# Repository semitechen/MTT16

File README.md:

**⚠️WARNING⚠️**  
This is a "Work in progress" project.
Read all the documentation before proceeding with development.

# Hardware Tracker MIDI Sequencer

A hardware-style MIDI sequencer designed for DJs and home producers. This device combines tactile control with powerful features to streamline music creation and performance.

---

## Features

### 🎵 Tracks & MIDI Control
- **16 Tracks**: Each track consists of 4 bytes:  
  - **Byte 1**: Type and channel  
  - **Byte 2**: Data byte 1 (note) 
  - **Byte 3**: Data byte 2 (velocity)
  - **Byte 4**: Delay  
- **Editing**: Tracks can be edited and muted via dedicated keypads.

### 🔄 Magnetic Encoder & Sync Control
- **Magnetic Encoder**:  
  - Control track position.  
  - Sync with song tempo "vinyl style".  
  - **Shift Key** under the encoder for alternate functions.  

### 🎚️ Tempo Control
- **Tempo Fader**: Fine-tune playback tempo.  
- **Tempo Modes**:  
  - Select tempo control range (+8, +16, wide) via buttons and LED indicators.

### ⌨️ Keypads & Modes
#### 16-Key Cherry MX Keypad
- **Modes**:  
  - Edit mode (upcoming functionality).  
  - Mute mode: Mute individual tracks.

#### 8-Key Cherry MX Keypad 
| Key        | Shift Function   | 
|------------|------------------|
| Cue        | Play             |
| A          | Edit             |
| B          | Mute             |
| Scene      | New Scene        |
| Nudge      | Tempo            |
| Copy       | Paste            |
| Delete     | Undo             |
| OK         | Duplicate        |

### 📟 Display
- **8x32 7-Segment LED Display**:  
  - Each character is 0.28".  
  - Displays key information across 4 columns in Scene Mode:  
    - Original tempo  
    - Scene  
    - A track  
    - B track  

### 🎛️ Scene Mode
- Use **OK Key** to select a scene and assign it to **Track A** or **Track B** via the **A** and **B** keys.  
- Each scene comprises 16 editable tracks.  
- Select and edit tracks using the **16-Key Keypad** in Edit Mode.  

---

## 📸 Photos
_Add photos here._  

---

## License
This project is licensed under the [Creative Commons Attribution-NonCommercial-ShareAlike 4.0 International License](https://creativecommons.org/licenses/by-nc-sa/4.0/).  

- You are free to build and modify the hardware and software for **non-commercial purposes**.  
- Commercial use of this project is strictly prohibited.

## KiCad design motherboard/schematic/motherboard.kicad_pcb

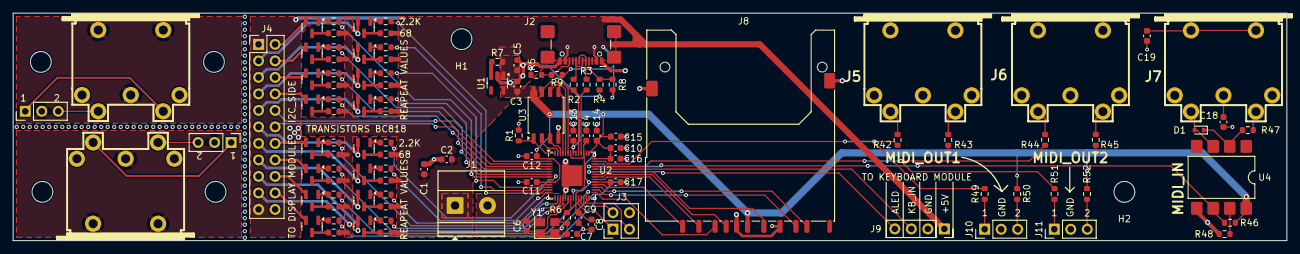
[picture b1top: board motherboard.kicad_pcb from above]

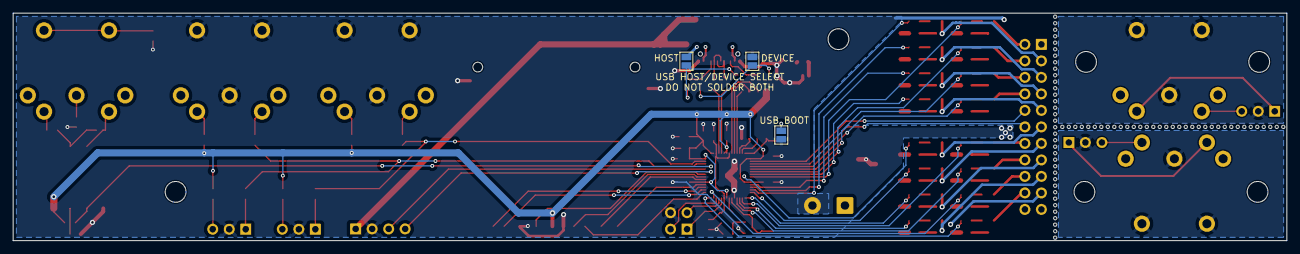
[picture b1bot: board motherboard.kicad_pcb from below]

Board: 2 copper layers, 196.0 x 35.0 mm, 117 parts (3 on the bottom side), 124 nets.

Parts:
C1: 100nF; C_0603_1608Metric
C2, C4, C5, C11: 1uF; C_0603_1608Metric
C3, C8, C9, C10, C12, C13, C14, C15, C16, C17: 0.1uF; C_0603_1608Metric
C6, C7: 15pF; C_0603_1608Metric
C18, C19: 0.1u; C_0603_1608Metric
D1: 1N4148WT; D_SOD-523
H1, H2: MountingHole; MountingHole_3.2mm_M3
H3, H4, H5, H6: Hole; MountingHole_3.2mm_M3
J1: Screw_Terminal_01x02; TerminalBlock_Phoenix_MKDS-1,5-2_1x02_P5.00mm_Horizontal
J2: USB_C_Receptacle_USB2.0_16P; USB_C_Receptacle_GCT_USB4110
J3: Conn_01x04; PinHeader_2x02_P2.54mm_Vertical
J4: Conn_02x11_Odd_Even; PinHeader_2x11_P2.54mm_Vertical
J5: MIDI_OUT1; MIDI_DIN5
J6: MIDI_OUT2; MIDI_DIN5
J7: MIDI_IN; MIDI_DIN5
J8: SD_Card_Receptacle; SD_Kyocera_145638009511859+
J9: Conn_01x04; PinSocket_1x04_P2.54mm_Vertical
J10, J11, J14, J15: Conn_01x03; PinHeader_1x03_P2.54mm_Vertical
J12, J13: MIDI_DIN5
JP1: USB_BOOT; SolderJumper-2_P1.3mm_Open_Pad1.0x1.5mm
JP2: DIVICE_MODE; SolderJumper-2_P1.3mm_Open_Pad1.0x1.5mm
JP3: HOST_MODE; SolderJumper-2_P1.3mm_Open_Pad1.0x1.5mm
Q1, Q2, Q3, Q4, Q5, Q6, Q7, Q8, Q9, Q10, Q11, Q12, Q13, Q14, Q15, Q16: BC818; SOT-23
R1, R6: 1K; R_0603_1608Metric
R2, R3: 27; R_0603_1608Metric
R4, R5: 5.1K; R_0603_1608Metric
R7: 10K; R_0603_1608Metric
R8, R9: 22K; R_0603_1608Metric
R10, R11, R12, R13, R18, R19, R20, R21, R26, R27, R28, R29, R34, R35, R36, R37: 68; R_0603_1608Metric
R14, R15, R16, R17, R22, R23, R24, R25, R30, R31, R32, R33, R38, R39, R40, R41, R46: 2.2K; R_0603_1608Metric
R42, R44, R49, R51: 10; R_0603_1608Metric
R43, R45, R50, R52: 33; R_0603_1608Metric
R47: 220; R_0603_1608Metric
R48: 4.7K; R_0603_1608Metric
U1: AP2112K-3.3; SOT-23-5
U2: RP2040; QFN-56-1EP_7x7mm_P0.4mm_EP3.2x3.2mm
U3: W25Q128JVS; SOIC-8_5.3x5.3mm_P1.27mm
U4: 6N138; SMDIP-8_W9.53mm
Y1: ABM8-272-T3; Crystal_SMD_Abracon_ABM8G-4Pin_3.2x2.5mm

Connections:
+1V1: C4.2, C8.1, C9.1, U2.23 (DVDD), U2.45 (VREG_VOUT), U2.50 (DVDD)
+3V3: C3.1, C10.1, C11.1, C12.1, C13.1, C14.1, C15.1, C16.1, C17.1, J8.4 (VDD), R43.1, R45.1, R46.1, R50.2, R52.2, U1.5 (VOUT), U2.1 (IOVDD), U2.10 (IOVDD), U2.22 (IOVDD), U2.33 (IOVDD), U2.42 (IOVDD), U2.43 (ADC_AVDD), U2.44 (VREG_IN), U2.48 (USB_VDD), U2.49 (IOVDD), U3.8 (VCC), U4.8 (VCC)
+5V: C1.2, C2.2, C5.1, J1.1, J2.A4 (VBUS), J2.A9 (VBUS), J2.B4 (VBUS), J2.B9 (VBUS), J4.19, J9.1, JP3.2 (B), R7.1, R10.1, R11.1, R12.1, R13.1, R18.1, R19.1, R20.1, R21.1, R26.1, R27.1, R28.1, R29.1, R34.1, R35.1, R36.1, R37.1, U1.1 (VIN)
/ALED: J9.4, U2.37 (GPIO25)
/DISPLAY_CONTROL/A1: R14.1, U2.8 (GPIO6)
/DISPLAY_CONTROL/A2: R15.1, U2.6 (GPIO4)
/DISPLAY_CONTROL/A3: R16.1, U2.5 (GPIO3)
/DISPLAY_CONTROL/A4: R17.1, U2.4 (GPIO2)
/DISPLAY_CONTROL/A5: R22.1, U2.16 (GPIO13)
/DISPLAY_CONTROL/A6: R23.1, U2.18 (GPIO15)
/DISPLAY_CONTROL/A7: R24.1, U2.27 (GPIO16)
/DISPLAY_CONTROL/A8: R25.1, U2.28 (GPIO17)
/DISPLAY_CONTROL/A9: R30.1, U2.13 (GPIO10)
/DISPLAY_CONTROL/A10: R31.1, U2.12 (GPIO9)
/DISPLAY_CONTROL/A11: R32.1, U2.11 (GPIO8)
/DISPLAY_CONTROL/A12: R33.1, U2.7 (GPIO5)
/DISPLAY_CONTROL/A13: R38.1, U2.9 (GPIO7)
/DISPLAY_CONTROL/A14: R39.1, U2.14 (GPIO11)
/DISPLAY_CONTROL/A15: R40.1, U2.15 (GPIO12)
/DISPLAY_CONTROL/A16: R41.1, U2.17 (GPIO14)
/DISPLAY_CONTROL/A_1: J4.2, Q1.2 (E)
/DISPLAY_CONTROL/A_2: J4.4, Q2.2 (E)
/DISPLAY_CONTROL/A_3: J4.6, Q3.2 (E)
/DISPLAY_CONTROL/A_4: J4.8, Q4.2 (E)
/DISPLAY_CONTROL/A_5: J4.14, Q5.2 (E)
/DISPLAY_CONTROL/A_6: J4.16, Q6.2 (E)
/DISPLAY_CONTROL/A_7: J4.18, Q7.2 (E)
/DISPLAY_CONTROL/A_8: J4.20, Q8.2 (E)
/DISPLAY_CONTROL/A_9: J4.3, Q9.2 (E)
/DISPLAY_CONTROL/A_10: J4.5, Q10.2 (E)
/DISPLAY_CONTROL/A_11: J4.7, Q11.2 (E)
/DISPLAY_CONTROL/A_12: J4.9, Q12.2 (E)
/DISPLAY_CONTROL/A_13: J4.11, Q13.2 (E)
/DISPLAY_CONTROL/A_14: J4.13, Q14.2 (E)
/DISPLAY_CONTROL/A_15: J4.15, Q15.2 (E)
/DISPLAY_CONTROL/A_16: J4.17, Q16.2 (E)
/DISPLAY_CONTROL/SCL: J4.12, U2.3 (GPIO1)
/DISPLAY_CONTROL/SDA: J4.10, U2.2 (GPIO0)
/GND1: J12.2, J12.6, J14.2
/GND2: J13.2, J13.6, J15.2
/KB_IN: J9.3, U2.38 (GPIO26_ADC0)
/MCU/CC1: J2.A5 (CC1), R4.1, R8.1
/MCU/CC2: J2.B5 (CC2), R5.1, R9.1
/MCU/GPIO18: J8.2 (CMD), U2.29 (GPIO18)
/MCU/GPIO19: J8.7 (DAT0), U2.30 (GPIO19)
/MCU/GPIO20: J8.8 (DAT1), U2.31 (GPIO20)
/MCU/GPIO21: J8.9 (DAT2), U2.32 (GPIO21)
/MCU/GPIO22: J8.1 (CD/DAT3), U2.34 (GPIO22)
/MCU/GPIO23: J8.10 (CARD_DETECT), U2.35 (GPIO23)
/MCU/GPIO24: J8.5 (CLK), U2.36 (GPIO24)
/MCU/GPIO27: R46.2, U2.39 (GPIO27_ADC1), U4.6 (VO2)
/MCU/QSPI_CS: R1.1, U2.56 (QSPI_SS), U3.1 (~CS)
/MCU/QSPI_SCK: U2.52 (QSPI_SCLK), U3.6 (CLK)
/MCU/QSPI_SD0: U2.53 (QSPI_SD0), U3.5 (DI/IO_{0})
/MCU/QSPI_SD1: U2.55 (QSPI_SD1), U3.2 (DO/IO_{1})
/MCU/QSPI_SD2: U2.54 (QSPI_SD2), U3.3 (~WP/IO_{2})
/MCU/QSPI_SD3: U2.51 (QSPI_SD3), U3.7 (~HOLD/~RESET/IO_{3})
/MCU/RUN: J3.3, U2.26 (RUN)
/MCU/SWCLK: J3.1, U2.24 (SWCLK)
/MCU/SWDIO: J3.2, U2.25 (SWD)
/MCU/USB_BOOT: JP1.1 (A), R1.2
/MCU/USB_N: J2.A7 (D-), J2.B7 (D-), R3.2
/MCU/USB_P: J2.A6 (D+), J2.B6 (D+), R2.2
/MCU/XIN: C6.1, U2.20 (XIN), Y1.1
/MCU/XOUT: R6.1, U2.21 (XOUT)
/MIDI_OUT1: R42.2, R49.2, U2.41 (GPIO29_ADC3)
/MIDI_OUT2: R44.2, R51.2, U2.40 (GPIO28_ADC2)
GND: C1.1, C2.1, C3.2, C4.1, C5.2, C6.2, C7.2, C8.2, C9.2, C10.2, C11.2, C12.2, C13.2, C14.2, C15.2, C16.2, C17.2, C18.1, C19.2, J1.2, J2.A1 (GND), J2.A12 (GND), J2.B1 (GND), J2.B12 (GND), J3.4, J4.1, J4.21, J5.2, J5.6, J6.2, J6.6, J8.3 (VSS), J8.6 (VSS), J8.12 (SHELL1), J8.13 (SHELL2), J9.2, J10.2, J11.2, JP1.2 (B), JP2.2 (B), R48.1, U1.2 (GND), U2.19 (TESTEN), U2.57 (GND), U3.4 (GND), U4.5 (GND), Y1.2, Y1.4
unnamed: C7.1, R6.2, Y1.3
unnamed: C18.2, J7.2
unnamed: C19.1, J7.6
unnamed: D1.2 (A), J7.4, U4.3 (C2)
unnamed: D1.1 (K), R47.2, U4.2 (C1)
unnamed: J5.4, R42.1
unnamed: J5.5, R43.2
unnamed: J6.4, R44.1
unnamed: J6.5, R45.2
unnamed: J7.5, R47.1
unnamed: J10.1, R49.1
unnamed: J10.3, R50.1
unnamed: J11.1, R51.1
unnamed: J11.3, R52.1
unnamed: J12.5, J14.1
unnamed: J12.4, J14.3
unnamed: J13.5, J15.1
unnamed: J13.4, J15.3
unnamed: JP2.1 (A), R4.2, R5.2
unnamed: JP3.1 (A), R8.2, R9.2
unnamed: Q1.1 (B), R14.2
unnamed: Q1.3 (C), R10.2
unnamed: Q2.1 (B), R15.2
unnamed: Q2.3 (C), R11.2
unnamed: Q3.1 (B), R16.2
unnamed: Q3.3 (C), R12.2
unnamed: Q4.1 (B), R17.2
unnamed: Q4.3 (C), R13.2
unnamed: Q5.1 (B), R22.2
unnamed: Q5.3 (C), R18.2
unnamed: Q6.1 (B), R23.2
unnamed: Q6.3 (C), R19.2
unnamed: Q7.1 (B), R24.2
unnamed: Q7.3 (C), R20.2
unnamed: Q8.1 (B), R25.2
unnamed: Q8.3 (C), R21.2
unnamed: Q9.1 (B), R30.2
unnamed: Q9.3 (C), R26.2
unnamed: Q10.1 (B), R31.2
unnamed: Q10.3 (C), R27.2
unnamed: Q11.1 (B), R32.2
unnamed: Q11.3 (C), R28.2
unnamed: Q12.1 (B), R33.2
unnamed: Q12.3 (C), R29.2
unnamed: Q13.1 (B), R38.2
unnamed: Q13.3 (C), R34.2
unnamed: Q14.1 (B), R39.2
unnamed: Q14.3 (C), R35.2
unnamed: Q15.1 (B), R40.2
unnamed: Q15.3 (C), R36.2
unnamed: Q16.1 (B), R41.2
unnamed: Q16.3 (C), R37.2
unnamed: R7.2, U1.3 (EN)
unnamed: R3.1, U2.46 (USB_DM)
unnamed: R2.1, U2.47 (USB_DP)
unnamed: R48.2, U4.7 (VO1)

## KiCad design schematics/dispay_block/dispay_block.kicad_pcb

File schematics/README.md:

# Hardware Tracker MIDI Sequencer

A hardware-style MIDI sequencer designed for DJs and home producers. This device combines tactile control with powerful features to streamline music creation and performance.

---

## Features

### 🎵 Tracks & MIDI Control
- **16 Tracks**: Each track consists of 4 bytes:  
  - **Byte 1**: Type and channel  
  - **Byte 2**: Data byte 1 (note) 
  - **Byte 3**: Data byte 2 (velocity)
  - **Byte 4**: Delay  
- **Editing**: Tracks can be edited and muted via dedicated keypads.

### 🔄 Magnetic Encoder & Sync Control
- **Magnetic Encoder**:  
  - Control track position.  
  - Sync with song tempo "vinyl style".  
  - **Shift Key** under the encoder for alternate functions.  

### 🎚️ Tempo Control
- **Tempo Fader**: Fine-tune playback tempo.  
- **Tempo Modes**:  
  - Select tempo control range (+8, +16, wide) via buttons and LED indicators.

### ⌨️ Keypads & Modes
#### 16-Key Cherry MX Keypad
- **Modes**:  
  - Edit mode (upcoming functionality).  
  - Mute mode: Mute individual tracks.

#### 8-Key Cherry MX Keypad 
| Key        | Shift Function   | 
|------------|------------------|
| Cue        | Play             |
| A          | Edit             |
| B          | Mute             |
| Scene      | New Scene        |
| Nudge      | Tempo            |
| Copy       | Paste            |
| Delete     | Undo             |
| OK         | Duplicate        |

### 📟 Display
- **8x32 7-Segment LED Display**:  
  - Each character is 0.28".  
  - Displays key information across 4 columns in Scene Mode:  
    - Original tempo  
    - Scene  
    - A track  
    - B track  

### 🎛️ Scene Mode
- Use **OK Key** to select a scene and assign it to **Track A** or **Track B** via the **A** and **B** keys.  
- Each scene comprises 16 editable tracks.  
- Select and edit tracks using the **16-Key Keypad** in Edit Mode.  

---

## 📸 Photos
_Add photos here._  

---

## License
This project is licensed under the [Creative Commons Attribution-NonCommercial-ShareAlike 4.0 International License](https://creativecommons.org/licenses/by-nc-sa/4.0/).  

- You are free to build and modify the hardware and software for **non-commercial purposes**.  
- Commercial use of this project is strictly prohibited.

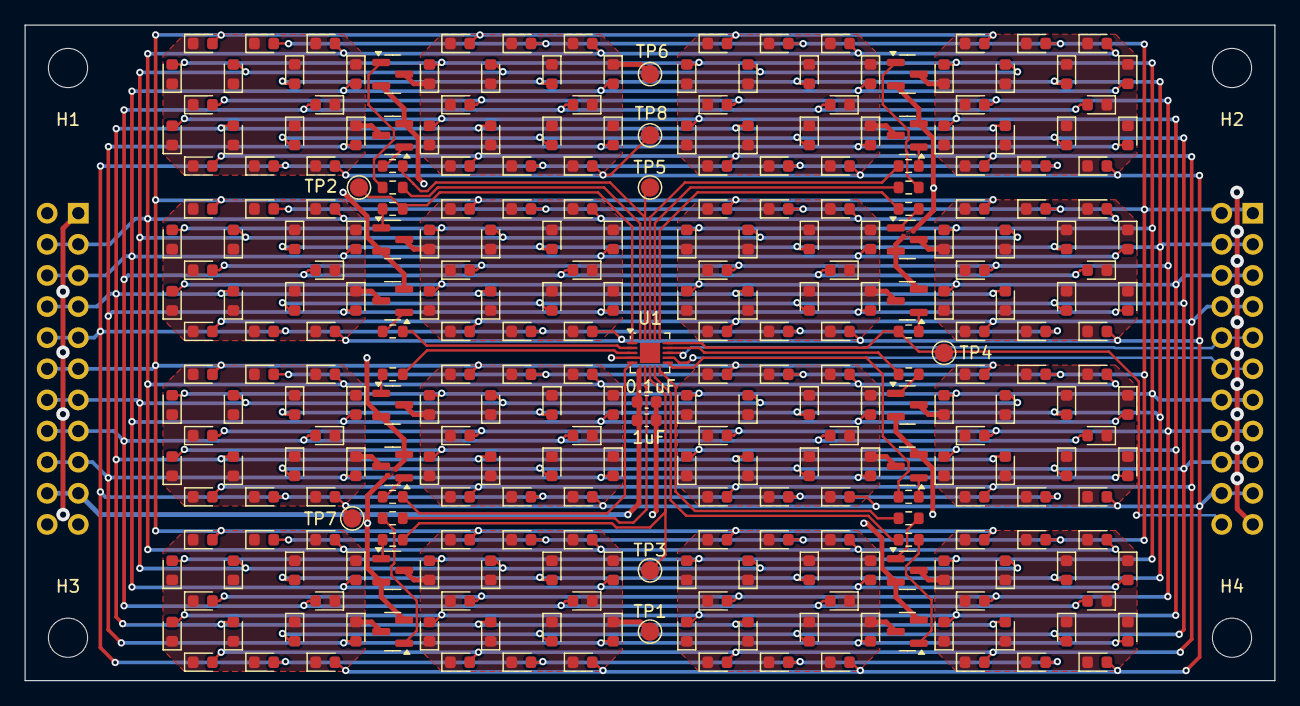
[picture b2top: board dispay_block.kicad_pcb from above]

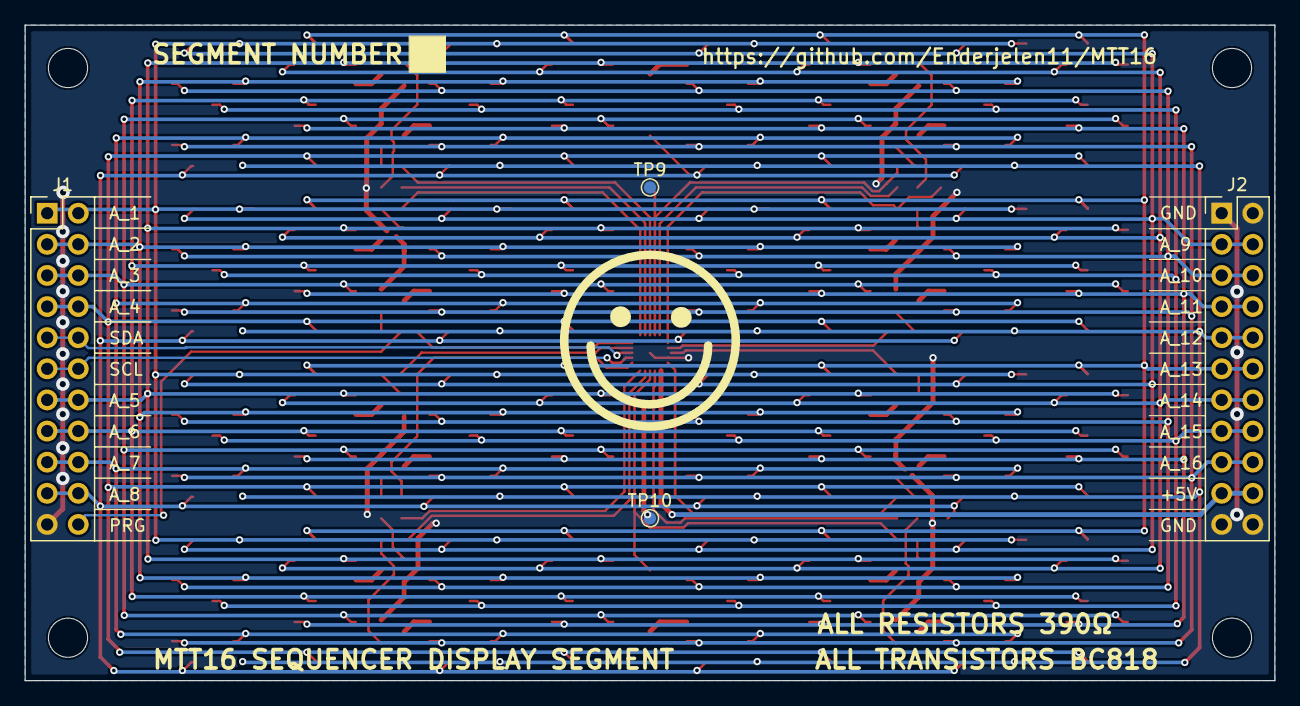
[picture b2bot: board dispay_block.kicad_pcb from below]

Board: 2 copper layers, 102.0 x 53.5 mm, 307 parts (4 on the bottom side), 68 nets.

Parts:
C1: 0.1uF; C_0603_1608Metric
C2: 1uF; C_0603_1608Metric
D1, D2, D3, D4, D5, D6, D7, D8, D9, D10, D11, D12, D13, D14, D15, D16, D17, D18, D19, D20, D21, D22, D23, D24, D25, D26, D27, D28, D29, D30, D31, D32, D33, D34, D35, D36, D37, D38, D39, D40, D41, D42, D43, D44, D45, D46, D47, D48, D49, D50, D51, D52, D53, D54, D55, D56, D57, D58, D59, D60, D61, D62, D63, D64, D65, D66, D67, D68, D69, D70, D71, D72, D73, D74, D75, D76, D77, D78, D79, D80, D81, D82, D83, D84, D85, D86, D87, D88, D89, D90, D91, D92, D93, D94, D95, D96, D97, D98, D99, D100, D101, D102, D103, D104, D105, D106, D107, D108, D109, D110, D111, D112, D113, D114, D115, D116, D117, D118, D119, D120, D121, D122, D123, D124, D125, D126, D127, D128, D129, D130, D131, D132, D133, D134, D135, D136, D137, D138, D139, D140, D141, D142, D143, D144, D145, D146, D147, D148, D149, D150, D151, D152, D153, D154, D155, D156, D157, D158, D159, D160, D161, D162, D163, D164, D165, D166, D167, D168, D169, D170, D171, D172, D173, D174, D175, D176, D177, D178, D179, D180, D181, D182, D183, D184, D185, D186, D187, D188, D189, D190, D191, D192, D193, D194, D195, D196, D197, D198, D199, D200, D201, D202, D203, D204, D205, D206, D207, D208, D209, D210, D211, D212, D213, D214, D215, D216, D217, D218, D219, D220, D221, D222, D223, D224, D225, D226, D227, D228, D229, D230, D231, D232, D233, D234, D235, D236, D237, D238, D239, D240, D241, D242, D243, D244, D245, D246, D247, D248, D249, D250, D251, D252, D253, D254, D255, D256: LED; LED_0603_1608Metric
H1, H2, H3, H4: MountingHole; MountingHole_3.2mm_M3
J1, J2: Conn_02x11_Odd_Even; PinHeader_2x11_P2.54mm_Vertical
Q1, Q2, Q3, Q4, Q5, Q6, Q7, Q8, Q9, Q10, Q11, Q12, Q13, Q14, Q15, Q16: BC818; SOT-23
R1, R2, R3, R4, R5, R6, R7, R8, R9, R10, R11, R12, R13, R14, R15, R16: 390; R_0603_1608Metric
TP1: CC13; TestPoint_Pad_D1.5mm
TP2: RESET; TestPoint_Pad_D1.5mm
TP3: PC1; TestPoint_Pad_D1.5mm
TP4: PD1(SWIO); TestPoint_Pad_D1.5mm
TP5: PD5(TX); TestPoint_Pad_D1.5mm
TP6: CC2; TestPoint_Pad_D1.5mm
TP7, TP8: B8; TestPoint_Pad_D1.5mm
TP9, TP10: GND; TestPoint_Pad_D1.0mm
U1: CH32V003FxUx; QFN-20-1EP_3x3mm_P0.4mm_EP1.65x1.65mm

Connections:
+5V: C1.2, C2.2, J2.19, J2.20, U1.6 (VDD)
/CC1: D1.1 (K), D2.1 (K), D3.1 (K), D4.1 (K), D5.1 (K), D6.1 (K), D7.1 (K), D8.1 (K), D9.1 (K), D10.1 (K), D11.1 (K), D12.1 (K), D13.1 (K), D14.1 (K), D15.1 (K), D16.1 (K), Q4.3 (C)
/CC2: D17.1 (K), D18.1 (K), D19.1 (K), D20.1 (K), D21.1 (K), D22.1 (K), D23.1 (K), D24.1 (K), D25.1 (K), D26.1 (K), D27.1 (K), D28.1 (K), D29.1 (K), D30.1 (K), D31.1 (K), D32.1 (K), Q5.3 (C), TP6.1
/CC3: D33.1 (K), D34.1 (K), D35.1 (K), D36.1 (K), D37.1 (K), D38.1 (K), D39.1 (K), D40.1 (K), D41.1 (K), D42.1 (K), D43.1 (K), D44.1 (K), D45.1 (K), D46.1 (K), D47.1 (K), D48.1 (K), Q8.3 (C)
/CC4: D49.1 (K), D50.1 (K), D51.1 (K), D52.1 (K), D53.1 (K), D54.1 (K), D55.1 (K), D56.1 (K), D57.1 (K), D58.1 (K), D59.1 (K), D60.1 (K), D61.1 (K), D62.1 (K), D63.1 (K), D64.1 (K), Q7.3 (C)
/CC5: D65.1 (K), D66.1 (K), D67.1 (K), D68.1 (K), D69.1 (K), D70.1 (K), D71.1 (K), D72.1 (K), D73.1 (K), D74.1 (K), D75.1 (K), D76.1 (K), D77.1 (K), D78.1 (K), D79.1 (K), D80.1 (K), Q14.3 (C)
/CC6: D81.1 (K), D82.1 (K), D83.1 (K), D84.1 (K), D85.1 (K), D86.1 (K), D87.1 (K), D88.1 (K), D89.1 (K), D90.1 (K), D91.1 (K), D92.1 (K), D93.1 (K), D94.1 (K), D95.1 (K), D96.1 (K), Q9.3 (C)
/CC7: D97.1 (K), D98.1 (K), D99.1 (K), D100.1 (K), D101.1 (K), D102.1 (K), D103.1 (K), D104.1 (K), D105.1 (K), D106.1 (K), D107.1 (K), D108.1 (K), D109.1 (K), D110.1 (K), D111.1 (K), D112.1 (K), Q10.3 (C)
/CC8: D113.1 (K), D114.1 (K), D115.1 (K), D116.1 (K), D117.1 (K), D118.1 (K), D119.1 (K), D120.1 (K), D121.1 (K), D122.1 (K), D123.1 (K), D124.1 (K), D125.1 (K), D126.1 (K), D127.1 (K), D128.1 (K), Q1.3 (C)
/CC9: D129.1 (K), D130.1 (K), D131.1 (K), D132.1 (K), D133.1 (K), D134.1 (K), D135.1 (K), D136.1 (K), D137.1 (K), D138.1 (K), D139.1 (K), D140.1 (K), D141.1 (K), D142.1 (K), D143.1 (K), D144.1 (K), Q6.3 (C)
/CC10: D145.1 (K), D146.1 (K), D147.1 (K), D148.1 (K), D149.1 (K), D150.1 (K), D151.1 (K), D152.1 (K), D153.1 (K), D154.1 (K), D155.1 (K), D156.1 (K), D157.1 (K), D158.1 (K), D159.1 (K), D160.1 (K), Q16.3 (C)
/CC11: D161.1 (K), D162.1 (K), D163.1 (K), D164.1 (K), D165.1 (K), D166.1 (K), D167.1 (K), D168.1 (K), D169.1 (K), D170.1 (K), D171.1 (K), D172.1 (K), D173.1 (K), D174.1 (K), D175.1 (K), D176.1 (K), Q11.3 (C)
/CC12: D177.1 (K), D178.1 (K), D179.1 (K), D180.1 (K), D181.1 (K), D182.1 (K), D183.1 (K), D184.1 (K), D185.1 (K), D186.1 (K), D187.1 (K), D188.1 (K), D189.1 (K), D190.1 (K), D191.1 (K), D192.1 (K), Q2.3 (C)
/CC13: D193.1 (K), D194.1 (K), D195.1 (K), D196.1 (K), D197.1 (K), D198.1 (K), D199.1 (K), D200.1 (K), D201.1 (K), D202.1 (K), D203.1 (K), D204.1 (K), D205.1 (K), D206.1 (K), D207.1 (K), D208.1 (K), Q12.3 (C), TP1.1
/CC14: D209.1 (K), D210.1 (K), D211.1 (K), D212.1 (K), D213.1 (K), D214.1 (K), D215.1 (K), D216.1 (K), D217.1 (K), D218.1 (K), D219.1 (K), D220.1 (K), D221.1 (K), D222.1 (K), D223.1 (K), D224.1 (K), Q13.3 (C)
/CC15: D225.1 (K), D226.1 (K), D227.1 (K), D228.1 (K), D229.1 (K), D230.1 (K), D231.1 (K), D232.1 (K), D233.1 (K), D234.1 (K), D235.1 (K), D236.1 (K), D237.1 (K), D238.1 (K), D239.1 (K), D240.1 (K), Q15.3 (C)
/CC16: D241.1 (K), D242.1 (K), D243.1 (K), D244.1 (K), D245.1 (K), D246.1 (K), D247.1 (K), D248.1 (K), D249.1 (K), D250.1 (K), D251.1 (K), D252.1 (K), D253.1 (K), D254.1 (K), D255.1 (K), D256.1 (K), Q3.3 (C)
/SCL: J1.11, J1.12, U1.12 (SCL_2)
/SDA: J1.9, J1.10, U1.13 (SDA_2)
/SWIO: J1.22, R13.1, TP4.1, U1.15 (PD1)
A_1: D2.2 (A), D18.2 (A), D34.2 (A), D50.2 (A), D66.2 (A), D82.2 (A), D98.2 (A), D114.2 (A), D130.2 (A), D146.2 (A), D162.2 (A), D178.2 (A), D194.2 (A), D210.2 (A), D226.2 (A), D242.2 (A), J1.1, J1.2
A_2: D6.2 (A), D22.2 (A), D38.2 (A), D54.2 (A), D70.2 (A), D86.2 (A), D102.2 (A), D118.2 (A), D134.2 (A), D150.2 (A), D166.2 (A), D182.2 (A), D198.2 (A), D214.2 (A), D230.2 (A), D246.2 (A), J1.3, J1.4
A_3: D10.2 (A), D26.2 (A), D42.2 (A), D58.2 (A), D74.2 (A), D90.2 (A), D106.2 (A), D122.2 (A), D138.2 (A), D154.2 (A), D170.2 (A), D186.2 (A), D202.2 (A), D218.2 (A), D234.2 (A), D250.2 (A), J1.5, J1.6
A_4: D14.2 (A), D30.2 (A), D46.2 (A), D62.2 (A), D78.2 (A), D94.2 (A), D110.2 (A), D126.2 (A), D142.2 (A), D158.2 (A), D174.2 (A), D190.2 (A), D206.2 (A), D222.2 (A), D238.2 (A), D254.2 (A), J1.7, J1.8
A_5: D4.2 (A), D20.2 (A), D36.2 (A), D52.2 (A), D68.2 (A), D84.2 (A), D100.2 (A), D116.2 (A), D132.2 (A), D148.2 (A), D164.2 (A), D180.2 (A), D196.2 (A), D212.2 (A), D228.2 (A), D244.2 (A), J1.13, J1.14
A_6: D8.2 (A), D24.2 (A), D40.2 (A), D56.2 (A), D72.2 (A), D88.2 (A), D104.2 (A), D120.2 (A), D136.2 (A), D152.2 (A), D168.2 (A), D184.2 (A), D200.2 (A), D216.2 (A), D232.2 (A), D248.2 (A), J1.15, J1.16
A_7: D12.2 (A), D28.2 (A), D44.2 (A), D60.2 (A), D76.2 (A), D92.2 (A), D108.2 (A), D124.2 (A), D140.2 (A), D156.2 (A), D172.2 (A), D188.2 (A), D204.2 (A), D220.2 (A), D236.2 (A), D252.2 (A), J1.17, J1.18
A_8: D16.2 (A), D32.2 (A), D48.2 (A), D64.2 (A), D80.2 (A), D96.2 (A), D112.2 (A), D128.2 (A), D144.2 (A), D160.2 (A), D176.2 (A), D192.2 (A), D208.2 (A), D224.2 (A), D240.2 (A), D256.2 (A), J1.19, J1.20, TP7.1, TP8.1
A_9: D3.2 (A), D19.2 (A), D35.2 (A), D51.2 (A), D67.2 (A), D83.2 (A), D99.2 (A), D115.2 (A), D131.2 (A), D147.2 (A), D163.2 (A), D179.2 (A), D195.2 (A), D211.2 (A), D227.2 (A), D243.2 (A), J2.3, J2.4
A_10: D7.2 (A), D23.2 (A), D39.2 (A), D55.2 (A), D71.2 (A), D87.2 (A), D103.2 (A), D119.2 (A), D135.2 (A), D151.2 (A), D167.2 (A), D183.2 (A), D199.2 (A), D215.2 (A), D231.2 (A), D247.2 (A), J2.5, J2.6
A_11: D11.2 (A), D27.2 (A), D43.2 (A), D59.2 (A), D75.2 (A), D91.2 (A), D107.2 (A), D123.2 (A), D139.2 (A), D155.2 (A), D171.2 (A), D187.2 (A), D203.2 (A), D219.2 (A), D235.2 (A), D251.2 (A), J2.7, J2.8
A_12: D15.2 (A), D31.2 (A), D47.2 (A), D63.2 (A), D79.2 (A), D95.2 (A), D111.2 (A), D127.2 (A), D143.2 (A), D159.2 (A), D175.2 (A), D191.2 (A), D207.2 (A), D223.2 (A), D239.2 (A), D255.2 (A), J2.9, J2.10
A_13: D1.2 (A), D17.2 (A), D33.2 (A), D49.2 (A), D65.2 (A), D81.2 (A), D97.2 (A), D113.2 (A), D129.2 (A), D145.2 (A), D161.2 (A), D177.2 (A), D193.2 (A), D209.2 (A), D225.2 (A), D241.2 (A), J2.11, J2.12
A_14: D5.2 (A), D21.2 (A), D37.2 (A), D53.2 (A), D69.2 (A), D85.2 (A), D101.2 (A), D117.2 (A), D133.2 (A), D149.2 (A), D165.2 (A), D181.2 (A), D197.2 (A), D213.2 (A), D229.2 (A), D245.2 (A), J2.13, J2.14
A_15: D9.2 (A), D25.2 (A), D41.2 (A), D57.2 (A), D73.2 (A), D89.2 (A), D105.2 (A), D121.2 (A), D137.2 (A), D153.2 (A), D169.2 (A), D185.2 (A), D201.2 (A), D217.2 (A), D233.2 (A), D249.2 (A), J2.15, J2.16
A_16: D13.2 (A), D29.2 (A), D45.2 (A), D61.2 (A), D77.2 (A), D93.2 (A), D109.2 (A), D125.2 (A), D141.2 (A), D157.2 (A), D173.2 (A), D189.2 (A), D205.2 (A), D221.2 (A), D237.2 (A), D253.2 (A), J2.17, J2.18
GND: C1.1, C2.1, J1.21, J2.1, J2.2, J2.21, J2.22, Q1.2 (E), Q2.2 (E), Q3.2 (E), Q4.2 (E), Q5.2 (E), Q6.2 (E), Q7.2 (E), Q8.2 (E), Q9.2 (E), Q10.2 (E), Q11.2 (E), Q12.2 (E), Q13.2 (E), Q14.2 (E), Q15.2 (E), Q16.2 (E), TP9.1, TP10.1, U1.4 (VSS), U1.21 (VSS)
unnamed: Q1.1 (B), R5.2
unnamed: Q2.1 (B), R1.2
unnamed: Q3.1 (B), R15.1
unnamed: Q4.1 (B), R3.1
unnamed: Q5.1 (B), R4.1
unnamed: Q6.1 (B), R6.2
unnamed: Q7.1 (B), R7.2
unnamed: Q8.1 (B), R9.1
unnamed: Q9.1 (B), R11.1
unnamed: Q10.1 (B), R13.2
unnamed: Q11.1 (B), R14.2
unnamed: Q12.1 (B), R12.1
unnamed: Q13.1 (B), R10.2
unnamed: Q14.1 (B), R8.2
unnamed: Q15.1 (B), R2.1
unnamed: Q16.1 (B), R16.2
unnamed: R8.1, U1.2 (PA1)
unnamed: R16.1, U1.3 (PA2)
unnamed: R10.1, U1.7 (PC0)
unnamed: R12.2, TP3.1, U1.8 (PC1)
unnamed: R2.2, U1.9 (PC2)
unnamed: R15.2, U1.10 (PC3)
unnamed: R14.1, U1.11 (PC4)
unnamed: R1.1, U1.14 (PC7)
unnamed: R6.1, U1.5 (PD0)
unnamed: R5.1, U1.16 (PD2)
unnamed: R7.1, U1.17 (PD3)
unnamed: R9.2, U1.18 (PD4)
unnamed: R3.2, TP5.1, U1.19 (PD5)
unnamed: R4.2, U1.20 (PD6)
unnamed: R11.2, TP2.1, U1.1 (PD7)

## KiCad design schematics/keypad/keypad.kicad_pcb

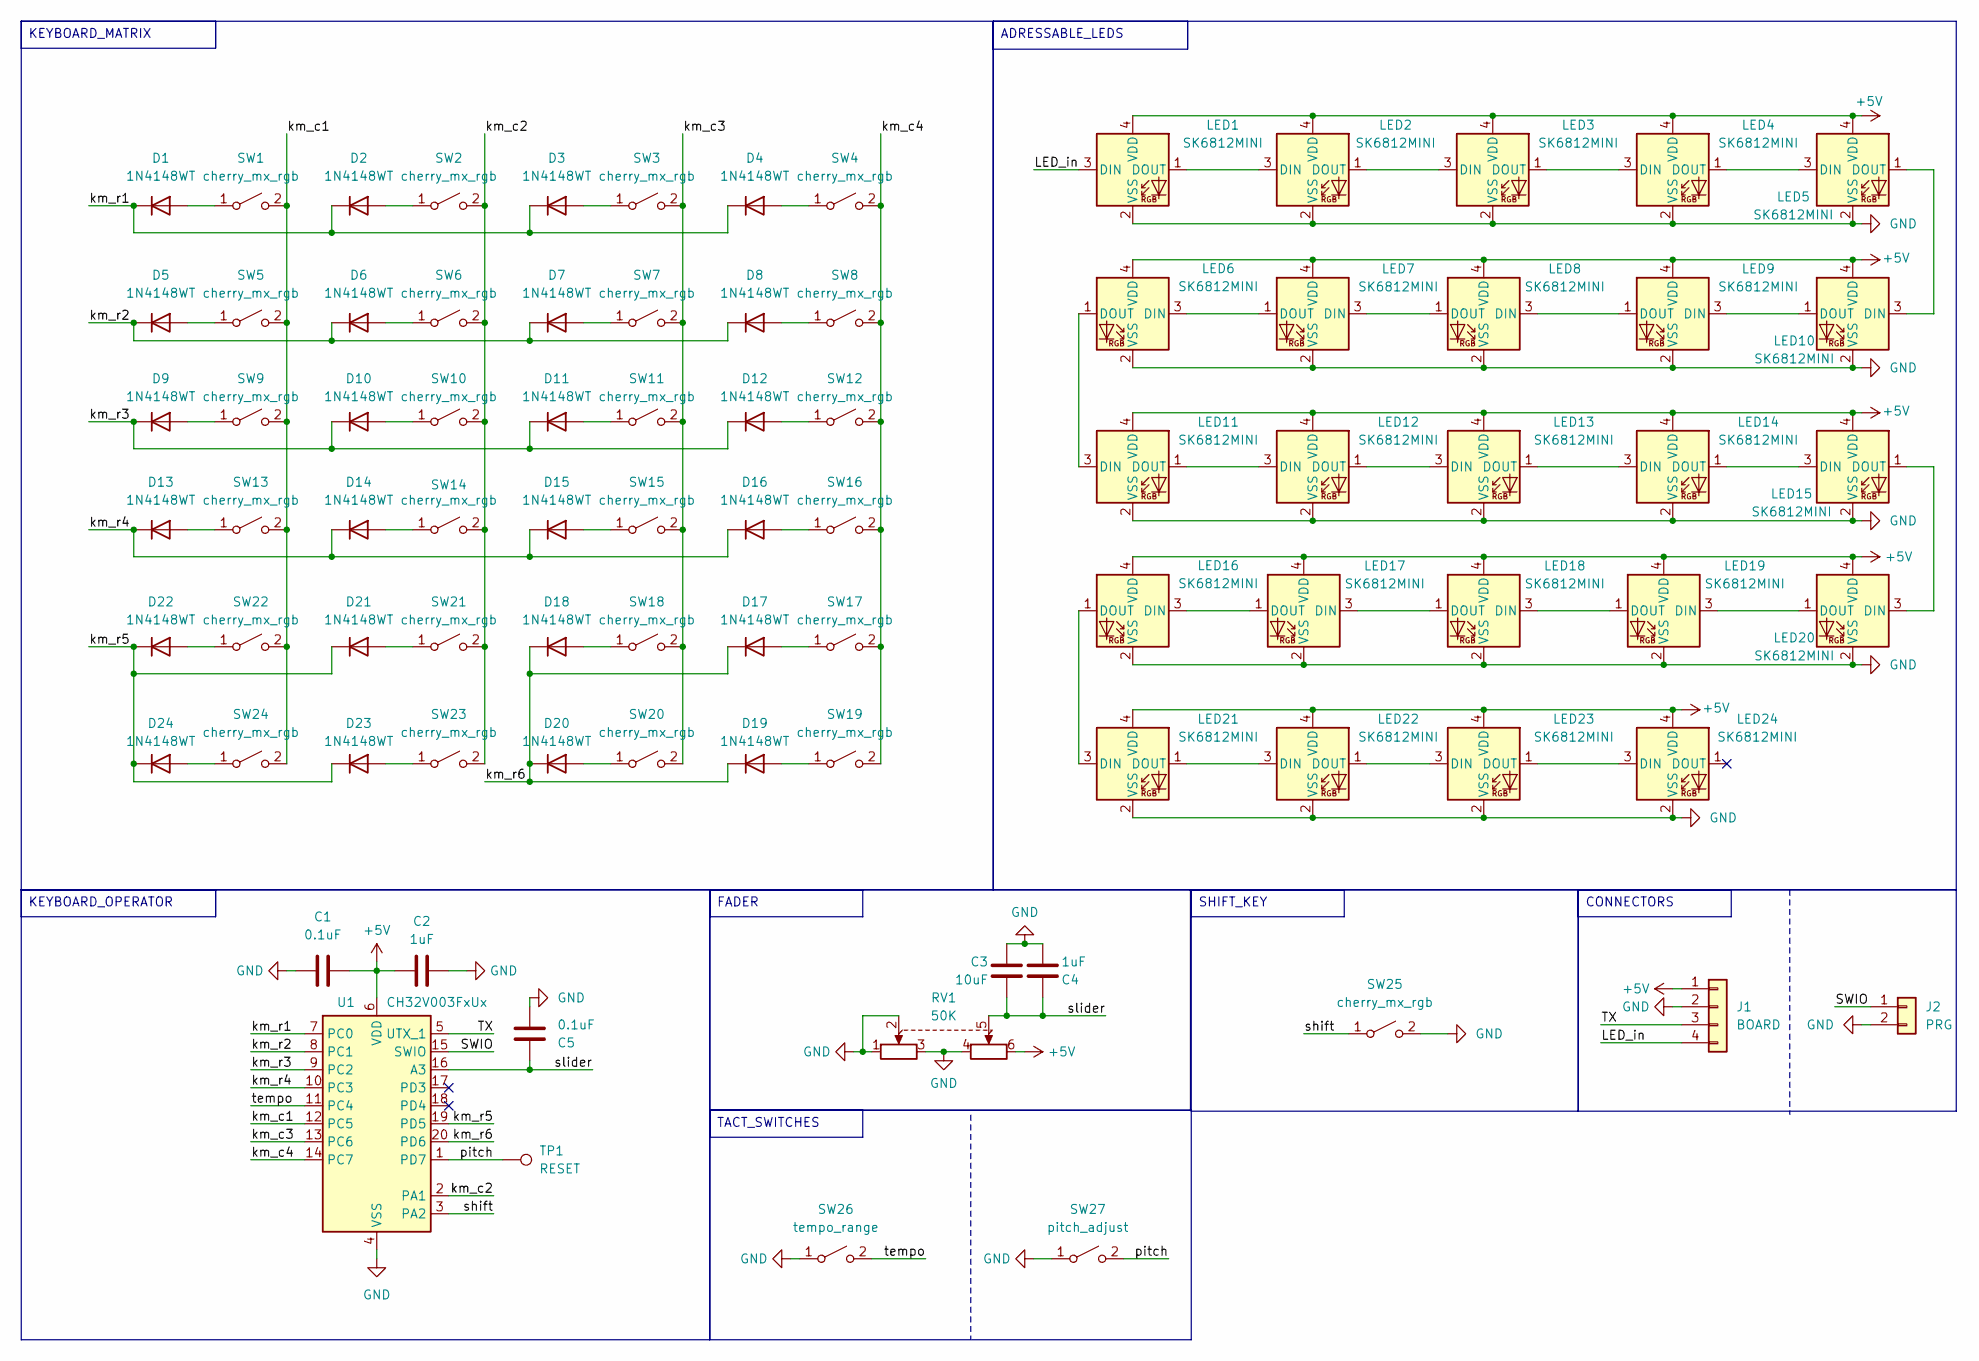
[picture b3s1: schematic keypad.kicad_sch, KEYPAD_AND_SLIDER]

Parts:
C1, C5: 0.1uF; C_0603_1608Metric
C2, C4: 1uF; C_0603_1608Metric
C3: 10uF; C_0603_1608Metric
D1, D2, D3, D4, D5, D6, D7, D8, D9, D10, D11, D12, D13, D14, D15, D16, D17, D18, D19, D20, D21, D22, D23, D24: 1N4148WT; D_SOD-523
J1: BOARD; PinHeader_1x04_P2.54mm_Horizontal; Part Number 1-0401FBV0T
J2: PRG; PinHeader_1x02_P2.54mm_Vertical; Part Number 1-0201FBV0T
LED1, LED2, LED3, LED4, LED5, LED6, LED7, LED8, LED9, LED10, LED11, LED12, LED13, LED14, LED15, LED16, LED17, LED18, LED19, LED20, LED21, LED22, LED23, LED24: SK6812MINI; SK6812-MINI-E
RV1: 50K; 75mm_slide_pot
SW1, SW2, SW3, SW4, SW5, SW6, SW7, SW8, SW9, SW10, SW11, SW12, SW13, SW14, SW15, SW16, SW17, SW18, SW19, SW20, SW21, SW22, SW23, SW24: cherry_mx_rgb; SW_Hotswap_Kailh_MX_1.00u
SW25: cherry_mx_rgb; SW_Hotswap_Kailh_MX_2.00u
SW26: tempo_range; tact_switch
SW27: pitch_adjust; tact_switch
TP1: RESET
U1: CH32V003FxUx; QFN-20-1EP_3x3mm_P0.4mm_EP1.65x1.65mm

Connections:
+5V: C1.2, C2.2, J1.1, LED1.4 (VDD), LED2.4 (VDD), LED3.4 (VDD), LED4.4 (VDD), LED5.4 (VDD), LED6.4 (VDD), LED7.4 (VDD), LED8.4 (VDD), LED9.4 (VDD), LED10.4 (VDD), LED11.4 (VDD), LED12.4 (VDD), LED13.4 (VDD), LED14.4 (VDD), LED15.4 (VDD), LED16.4 (VDD), LED17.4 (VDD), LED18.4 (VDD), LED19.4 (VDD), LED20.4 (VDD), LED21.4 (VDD), LED22.4 (VDD), LED23.4 (VDD), LED24.4 (VDD), RV1.6, U1.6 (VDD)
/LED_in: J1.4, LED1.3 (DIN)
/SWIO: J2.1, U1.15 (SWIO)
/TX: J1.3, U1.5 (UTX_1)
/km_c1: SW1.2 (B), SW5.2 (B), SW9.2 (B), SW13.2 (B), SW22.2 (B), SW24.2 (B), U1.12 (PC5)
/km_c2: SW2.2 (B), SW6.2 (B), SW10.2 (B), SW14.2 (B), SW21.2 (B), SW23.2 (B), U1.2 (PA1)
/km_c3: SW3.2 (B), SW7.2 (B), SW11.2 (B), SW15.2 (B), SW18.2 (B), SW20.2 (B), U1.13 (PC6)
/km_c4: SW4.2 (B), SW8.2 (B), SW12.2 (B), SW16.2 (B), SW17.2 (B), SW19.2 (B), U1.14 (PC7)
/km_r1: D1.1 (K), D2.1 (K), D3.1 (K), D4.1 (K), U1.7 (PC0)
/km_r2: D5.1 (K), D6.1 (K), D7.1 (K), D8.1 (K), U1.8 (PC1)
/km_r3: D9.1 (K), D10.1 (K), D11.1 (K), D12.1 (K), U1.9 (PC2)
/km_r4: D13.1 (K), D14.1 (K), D15.1 (K), D16.1 (K), U1.10 (PC3)
/km_r5: D21.1 (K), D22.1 (K), D23.1 (K), D24.1 (K), U1.19 (PD5)
/km_r6: D17.1 (K), D18.1 (K), D19.1 (K), D20.1 (K), U1.20 (PD6)
/pitch: SW27.2 (B), TP1.1, U1.1 (PD7)
/shift: SW25.1 (A), U1.3 (PA2)
/slider: C3.2, C4.1, C5.2, RV1.5, U1.16 (A3)
/tempo: SW26.2 (B), U1.11 (PC4)
GND: C1.1, C2.1, C3.1, C4.2, C5.1, J1.2, J2.2, LED1.2 (VSS), LED2.2 (VSS), LED3.2 (VSS), LED4.2 (VSS), LED5.2 (VSS), LED6.2 (VSS), LED7.2 (VSS), LED8.2 (VSS), LED9.2 (VSS), LED10.2 (VSS), LED11.2 (VSS), LED12.2 (VSS), LED13.2 (VSS), LED14.2 (VSS), LED15.2 (VSS), LED16.2 (VSS), LED17.2 (VSS), LED18.2 (VSS), LED19.2 (VSS), LED20.2 (VSS), LED21.2 (VSS), LED22.2 (VSS), LED23.2 (VSS), LED24.2 (VSS), RV1.1, RV1.2, RV1.3, RV1.4, SW25.2 (B), SW26.1 (A), SW27.1 (A), U1.4 (VSS), U1.21 (VSS)
unnamed: D1.2 (A), SW1.1 (A)
unnamed: D2.2 (A), SW2.1 (A)
unnamed: D3.2 (A), SW3.1 (A)
unnamed: D4.2 (A), SW4.1 (A)
unnamed: D5.2 (A), SW5.1 (A)
unnamed: D6.2 (A), SW6.1 (A)
unnamed: D7.2 (A), SW7.1 (A)
unnamed: D8.2 (A), SW8.1 (A)
unnamed: D9.2 (A), SW9.1 (A)
unnamed: D10.2 (A), SW10.1 (A)
unnamed: D11.2 (A), SW11.1 (A)
unnamed: D12.2 (A), SW12.1 (A)
unnamed: D13.2 (A), SW13.1 (A)
unnamed: D14.2 (A), SW14.1 (A)
unnamed: D15.2 (A), SW15.1 (A)
unnamed: D16.2 (A), SW16.1 (A)
unnamed: D17.2 (A), SW17.1 (A)
unnamed: D18.2 (A), SW18.1 (A)
unnamed: D19.2 (A), SW19.1 (A)
unnamed: D20.2 (A), SW20.1 (A)
unnamed: D21.2 (A), SW21.1 (A)
unnamed: D22.2 (A), SW22.1 (A)
unnamed: D23.2 (A), SW23.1 (A)
unnamed: D24.2 (A), SW24.1 (A)
unnamed: LED1.1 (DOUT), LED2.3 (DIN)
unnamed: LED2.1 (DOUT), LED3.3 (DIN)
unnamed: LED3.1 (DOUT), LED4.3 (DIN)
unnamed: LED4.1 (DOUT), LED5.3 (DIN)
unnamed: LED6.3 (DIN), LED7.1 (DOUT)
unnamed: LED7.3 (DIN), LED8.1 (DOUT)
unnamed: LED8.3 (DIN), LED9.1 (DOUT)
unnamed: LED5.1 (DOUT), LED10.3 (DIN)
unnamed: LED9.3 (DIN), LED10.1 (DOUT)
unnamed: LED6.1 (DOUT), LED11.3 (DIN)
unnamed: LED11.1 (DOUT), LED12.3 (DIN)
unnamed: LED12.1 (DOUT), LED13.3 (DIN)
unnamed: LED13.1 (DOUT), LED14.3 (DIN)
unnamed: LED14.1 (DOUT), LED15.3 (DIN)
unnamed: LED15.1 (DOUT), LED20.3 (DIN)
unnamed: LED16.3 (DIN), LED17.1 (DOUT)
unnamed: LED16.1 (DOUT), LED21.3 (DIN)
unnamed: LED17.3 (DIN), LED18.1 (DOUT)
unnamed: LED18.3 (DIN), LED19.1 (DOUT)
unnamed: LED19.3 (DIN), LED20.1 (DOUT)
unnamed: LED21.1 (DOUT), LED22.3 (DIN)
unnamed: LED22.1 (DOUT), LED23.3 (DIN)
unnamed: LED23.1 (DOUT), LED24.3 (DIN)

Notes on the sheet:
CONNECTORS
TACT_SWITCHES
SHIFT_KEY
FADER
KEYBOARD_MATRIX
ADRESSABLE_LEDS
KEYBOARD_OPERATOR

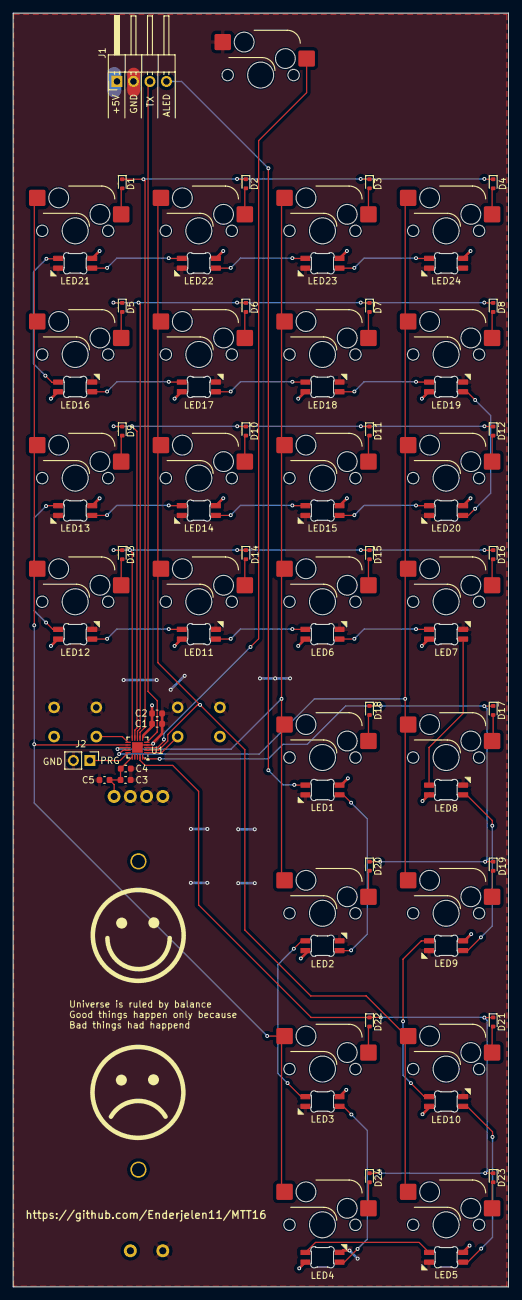
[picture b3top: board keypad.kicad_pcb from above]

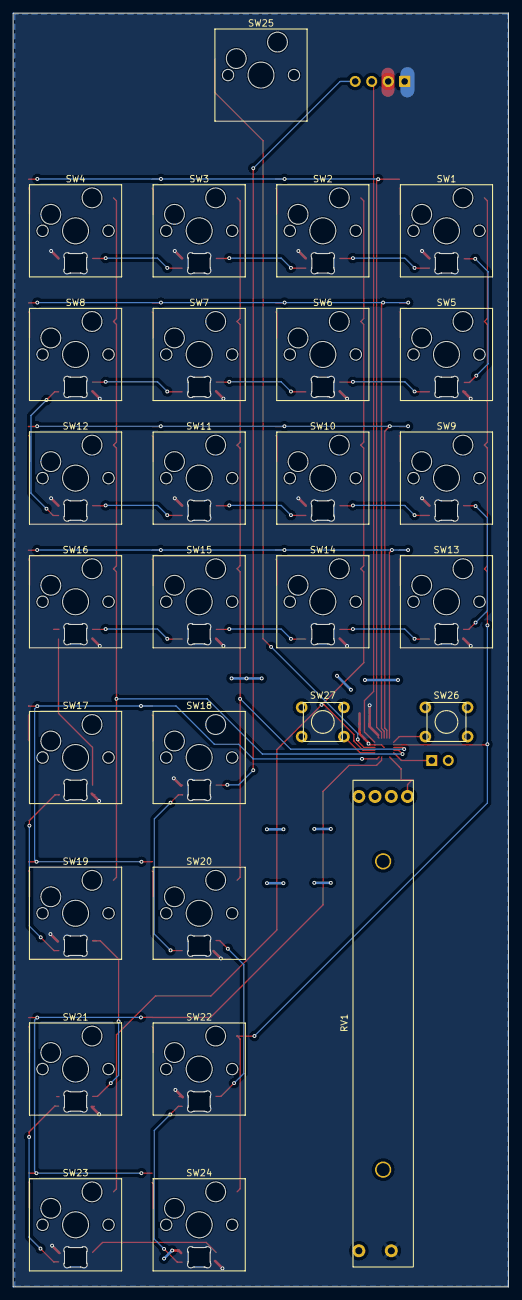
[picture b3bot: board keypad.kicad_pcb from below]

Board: 2 copper layers, 76.3 x 196.2 mm, 84 parts (28 on the bottom side), 66 nets.

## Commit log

2026-04-05 chore: initial commit with README and KiCad ignore
2026-04-05 docs: update README
2026-04-05 hw: add initial display schematic
2026-04-05 chore: add KiCad lock files to gitignore
2026-04-05 hw: annotate schematics and add capacitor footprints
2026-04-05 fix(hw): correct SK6812 LED footprint
2026-04-05 hw: add slider potentiometer footprint
2026-04-05 hw: add tact switch footprint
2026-04-05 fix(hw): adjust silkscreen for JLCPCB capabilities
2026-04-05 hw: add display segment schematic and PCB v1
2026-04-05 hw: add footprint library for MIDI, sliders, and SK6812
2026-04-05 hw: add keypad schematic
2026-04-05 fix(hw): update keypad silkscreen
2026-04-05 fix(hw): correct display block silkscreen
2026-04-05 hw: add MIDI DIN symbol and update footprint
2026-04-05 hw: add mouse bite footprint and fix MIDI DIN
2026-04-05 hw: add RP2350 footprint
2026-04-05 chore(hw): migrate display block to KiCad v9
2026-04-05 hw: add RP2350A symbol
2026-04-05 chore(hw): remove 3D models folder
2026-04-05 chore(hw): migrate keypad to KiCad v9
2026-04-05 hw: add encoder support to keypad
2026-04-05 hw: revise display design and fix wrong footprint
2026-04-05 hw: add motherboard PCB
2026-04-05 chore: remove accidentally committed file
2026-04-05 chore: restructure project folder layout
2026-04-05 chore: add Pico SDK submodule
2026-04-05 chore: add C build files to gitignore
2026-04-05 feat: add base firmware for motherboard
2026-04-05 feat: add sequential segment code for display block
2026-04-05 chore: update CH32V003 submodule
2026-04-05 docs: add programming instructions
2026-04-05 feat: allow selecting display block via make BLOCK=[NUM]
2026-04-05 chore: add CH32V003 library submodule
2026-04-05 chore: add clangd configuration
2026-04-05 fix: add parentheses to display block defines
2026-04-05 docs: add hardware incompatibility warning for SD lib
2026-04-05 chore: remove SD warning (now handled by CMake)
2026-04-05 feat: add load event for song management
2026-04-05 feat: support dual-port MIDI playback from memory
2026-04-05 feat: add base MIDI parser
2026-04-05 feat: integrate SD card library with PIO patch
2026-04-05 refactor: extract shared data and functions
2026-04-05 style: enforce hard tab indentation
2026-04-05 feat: add empty song initialization
2026-04-05 feat: implement MIDI out via DMA
2026-04-05 refactor: use song IDs instead of file paths
2026-04-05 perf: use event pool to prevent heap fragmentation
2026-04-05 test: add temporary display driver and manager
2026-04-05 fix: resolve PIO/DMA resource collisions
2026-04-05 chore: rename midi module to sequencer
2026-04-05 feat: implement clean stop with all notes off
2026-04-05 refactor: restructure into layered app/services/drivers
2026-04-05 refactor: decouple sequencer from storage via callbacks
2026-04-05 feat: implement base sequencer and multi-song playback
2026-04-05 chore: add custom flash target for picotool
2026-04-05 refactor: encapsulate global state and add accessor APIs
